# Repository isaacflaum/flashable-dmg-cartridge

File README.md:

# flashable-dmg-cartridge
PCB - Cartridge for original gameboy games with no mapper

This pcb is for flashing DMG games with no mapper such as the original Tetris game, or custom roms. The board is designed to take a PLCC-32 Socket + EEPROM Chip which can be removed from the socket and re-flashed to change gameboy ROMs. In order to make this cartridge you will need some soldering experience or determination plus the items listed in the BOM.

PCB is ready to be fabricated from anyone who takes gerber files - my fabricator of choice is PCBWay as they are professional and relatively quick. Feel free to open the files in KiCad and explore, modify and make your own variations of the board :) If you want to just fabricate what's already there you can upload the gerber.zip to PCBWay or any fabricator that takes gerber files. Make sure the following is specified (Note: if you are using another fabricator besides PCBWay this might vary):

* min via size is 0.3mm
* board thickness set to 0.8mm
* edge connector set to yes and 45 degree bevel with ENIG surface finish
* ENIG surface finish for the rest of the board (Note: You can use HASL which is a bit cheaper but wears out much quicker and is recommended against)

To flash a ROM onto the AT28C256 EEPROM Chip you will need a PLCC-32 to DIP-32 Adapter plus a flasher to program the chip. I use the same flasher paired with the Xgpro software that is used in this video: https://youtu.be/I4J-uNeLFRU?t=375 - make sure you are at least somewhat comfortable with what's going on in the video from ~6:15 - 7:15. The above video is great for getting familiar with flashing ROM chips. In the video, the chip being flashed is not electronically erasable and so a UV light is needed whereas we can blank our AT28C256 directly from Xgpro. Once the rom is flashed, verified and the PLCC-32 socket is soldered onto the board you can pop the rom chip in and plug the cartridge into any ol' gameboy - enjoy!

## BOM
| Refrence Designator | Part | Description | Link |
| :---: | :---: | :---: | --- |
| U1 | AT28C256-15JU | 32K 5V EEPROM Chip | https://www.mouser.com/ProductDetail/Microchip-Technology-Atmel/AT28C256-15JU?qs=MAR%2F2X5XOp4ElE%2FW%2FWXg2A%3D%3D
| U1 | 69802-432LF | PLCC-32 Socket | https://www.mouser.com/ProductDetail/Amphenol-FCI/69802-432LF?qs=kJUkXSjFC7xj%252BQ7fu6pp%2Fg%3D%3D
| C1 | C1206C106K4PACTU | 10 μF Capacitor | https://www.mouser.com/ProductDetail/80-C1206C106K4P
| R1 | ERA-8AEB123V | 12 kΩ 0.1% Resistor | https://www.mouser.com/ProductDetail/667-ERA-8AEB123V

# Cartridge Preview

## Front

## Back

# Schematic

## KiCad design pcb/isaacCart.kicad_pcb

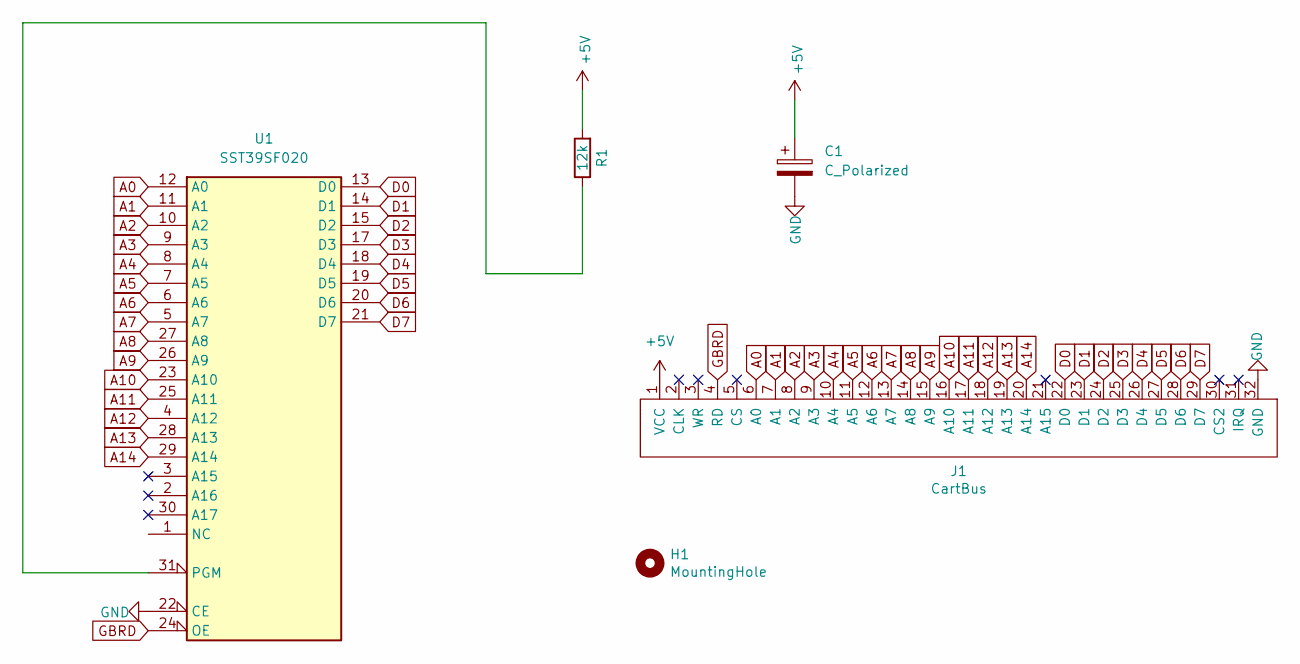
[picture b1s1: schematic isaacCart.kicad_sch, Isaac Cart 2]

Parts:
C1: C_Polarized; CP_EIA-3216-18_Kemet-A
H1: MountingHole; MountingHole_7mm
J1: CartBus; cartridge_PCBedge
R1: 12k; R_1206_3216Metric
U1: SST39SF020; PLCC-32_11.4x14.0mm_P1.27mm_SOCKET

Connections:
+5V: C1.1, J1.1 (VCC), R1.2, U1.32 (VCC)
A0: J1.6 (A0), U1.12 (A0)
A1: J1.7 (A1), U1.11 (A1)
A2: J1.8 (A2), U1.10 (A2)
A3: J1.9 (A3), U1.9 (A3)
A4: J1.10 (A4), U1.8 (A4)
A5: J1.11 (A5), U1.7 (A5)
A6: J1.12 (A6), U1.6 (A6)
A7: J1.13 (A7), U1.5 (A7)
A8: J1.14 (A8), U1.27 (A8)
A9: J1.15 (A9), U1.26 (A9)
A10: J1.16 (A10), U1.23 (A10)
A11: J1.17 (A11), U1.25 (A11)
A12: J1.18 (A12), U1.4 (A12)
A13: J1.19 (A13), U1.28 (A13)
A14: J1.20 (A14), U1.29 (A14)
D0: J1.22 (D0), U1.13 (D0)
D1: J1.23 (D1), U1.14 (D1)
D2: J1.24 (D2), U1.15 (D2)
D3: J1.25 (D3), U1.17 (D3)
D4: J1.26 (D4), U1.18 (D4)
D5: J1.27 (D5), U1.19 (D5)
D6: J1.28 (D6), U1.20 (D6)
D7: J1.29 (D7), U1.21 (D7)
GBRD: J1.4 (RD), U1.24 (OE)
GND: C1.2, J1.32 (GND), U1.16 (GND), U1.22 (CE)
unnamed: R1.1, U1.31 (PGM)

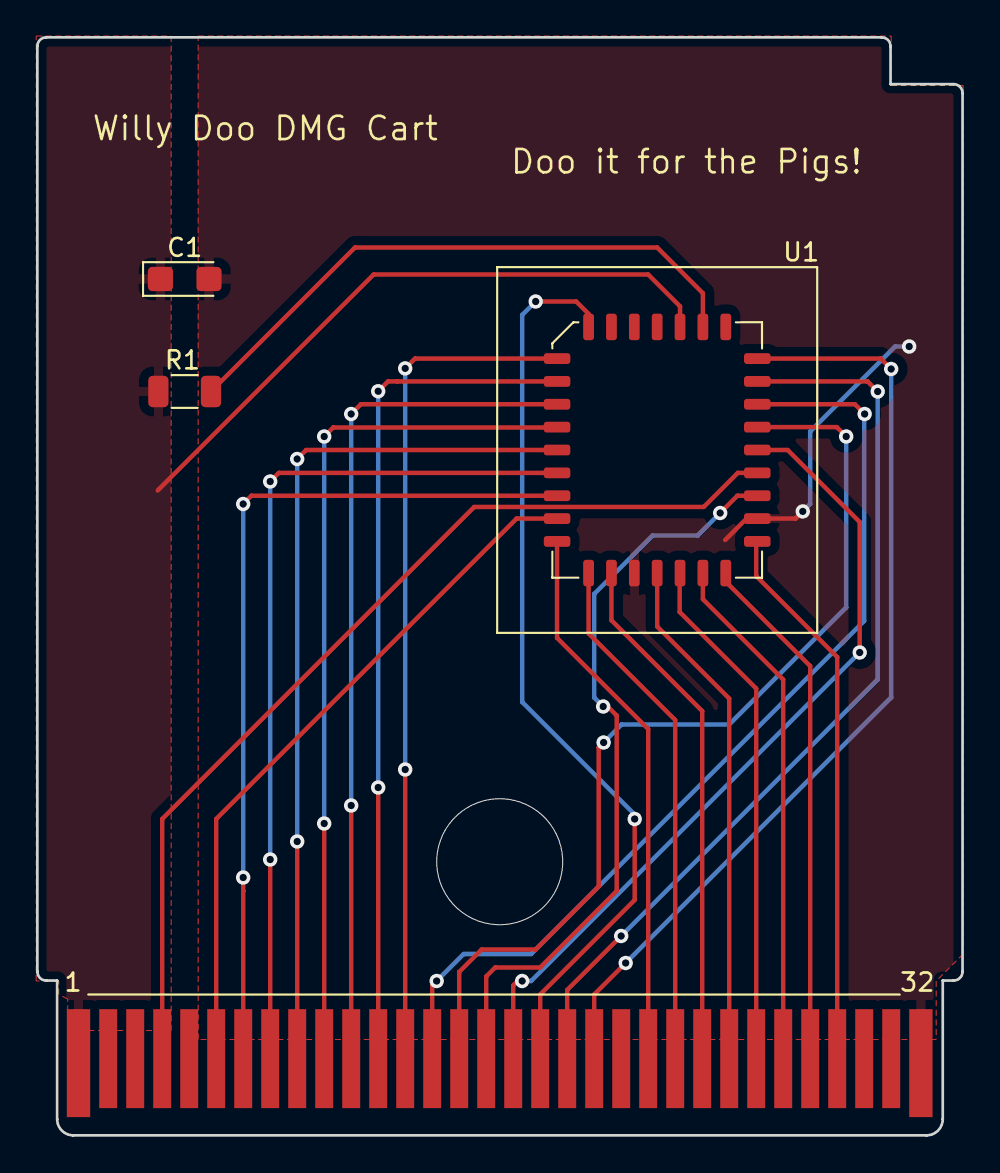
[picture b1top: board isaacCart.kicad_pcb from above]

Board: 2 copper layers, 51.4 x 61.0 mm, 5 parts (0 on the bottom side), 27 nets.

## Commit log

2022-10-29 Initial commit of cartridge version 1.0
2022-10-30 Update readme with BOM + fabrication instructions
2022-10-31 So we include drill files + gerber compatibility for pcbway
2022-10-31 updated front and back images of cartridge
2022-10-31 minor changes to make readme more legible
2022-11-05 New schematic + Board layout based on SST39SF020 PLCC-32 flash chip layout
2022-11-05 Update gerber files to match flash layout
2022-11-12 Increase silkscreen text size
